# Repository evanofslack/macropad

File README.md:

# MacroPad

Macropad utilizing the Raspberry Pi Pico. 3 layers of functionality, 6 switches, and 1 rotary encoder switch. Implements CircuitPython HID libraries and Adafruit matrix keypad library. Custom PCB designed in KiCAD (Gerbers can be found in the folder). Custom case designed in SolidWorks featuring a lasercut acrylic plates and a 3D printed base.

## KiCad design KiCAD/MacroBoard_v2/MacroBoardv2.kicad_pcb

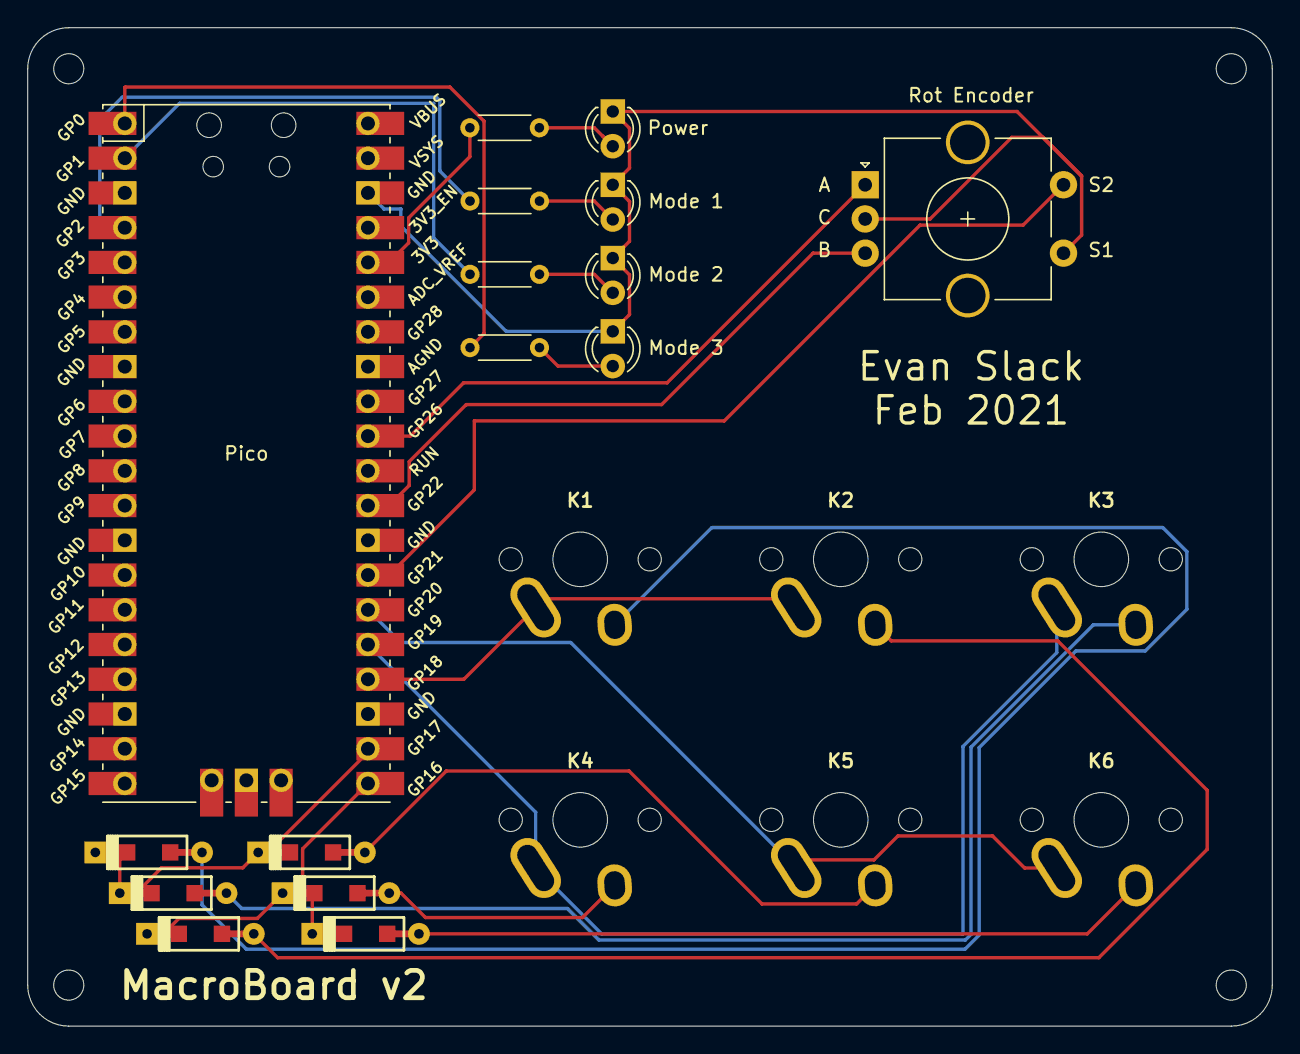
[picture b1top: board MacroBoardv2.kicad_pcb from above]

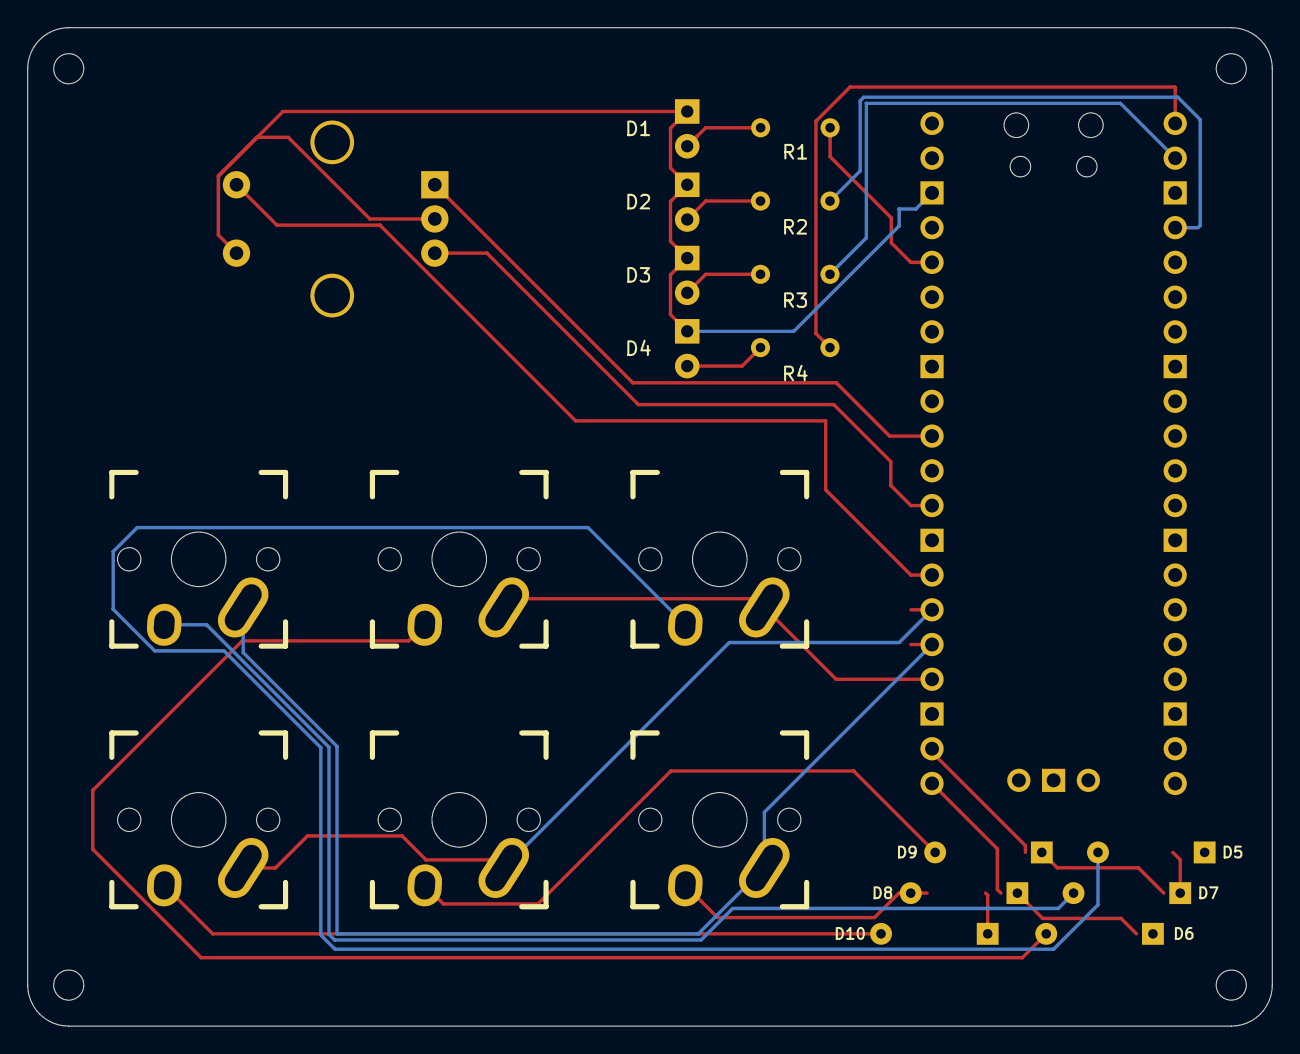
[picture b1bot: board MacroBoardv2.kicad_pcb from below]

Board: 2 copper layers, 91.0 x 73.0 mm, 22 parts (6 on the bottom side), 23 nets.

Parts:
D1, D2, D3, D4: LED; LED_D3.0mm
D5, D6, D7, D8, D9, D10: D; D_SOD123_axial
K1, K2, K3, K4, K5, K6: KEYSW; Mx_Alps_100
Pico: PICO_RP2040; RPi_Pico_SMD_TH
R1, R2, R3, R4: R; R_Axial_DIN0204_L3.6mm_D1.6mm_P5.08mm_Horizontal
Rot Encoder: Rotary_Encoder_Switch; RotaryEncoder_Alps_EC11E-Switch_Vertical_H20mm_CircularMoun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

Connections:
+5V: D1.1, D2.1, D3.1, D4.1, Pico.38, Rot Encoder.C, Rot Encoder.S1
/A_PIN: Pico.31, Rot Encoder.A
/B_PIN: Pico.29, Rot Encoder.B
/ROT_SW: Pico.27, Rot Encoder.S2
/col0: K1.1, K2.1, Pico.24
/col1: K3.1, K4.1, Pico.25
/col2: K5.1, K6.1, Pico.26
/row0: D5.1, D7.1, D9.1, Pico.22
unnamed: D1.2, R1.2
unnamed: D2.2, R2.1
unnamed: D3.2, R3.1
unnamed: D4.2, R4.1
unnamed: D5.2, K1.2
unnamed: D6.2, K2.2
unnamed: D7.2, K3.2
unnamed: D8.2, K4.2
unnamed: D9.2, K5.2
unnamed: D6.1, D8.1, D10.1, Pico.21
unnamed: D10.2, K6.2
unnamed: Pico.36, R1.1
unnamed: Pico.4, R2.2
unnamed: Pico.2, R3.2
unnamed: Pico.1, R4.2

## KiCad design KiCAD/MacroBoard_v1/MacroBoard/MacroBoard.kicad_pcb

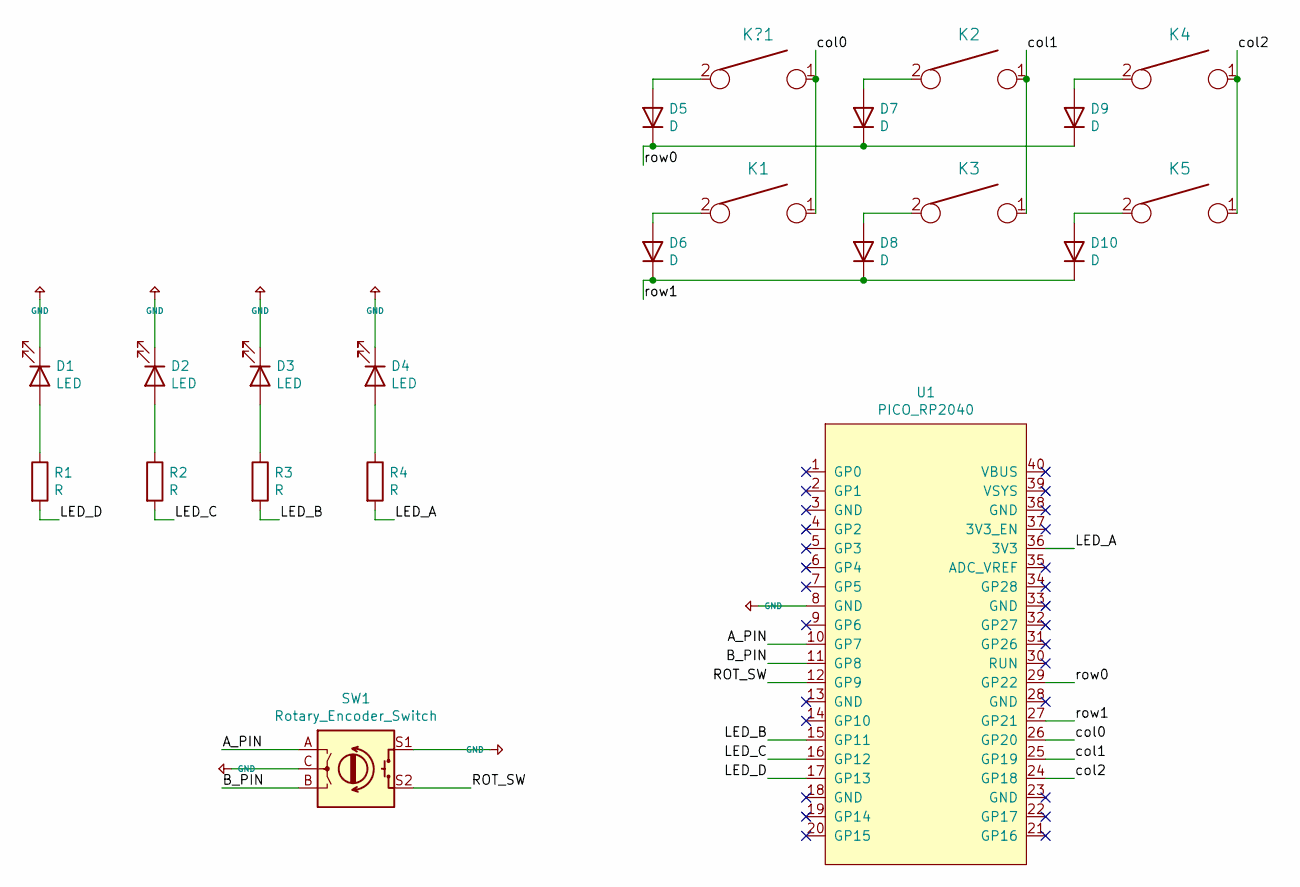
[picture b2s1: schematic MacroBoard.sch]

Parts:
D1, D2, D3, D4: LED; LED_D5.0mm
D5, D6, D7, D8, D9, D10: D; D_SOD123_axial
K1, K2, K3, K4, K5: KEYSW; Mx_Alps_100
K?1: KEYSW; Mx_Alps_100
R1, R2, R3, R4: R; R_Axial_DIN0204_L3.6mm_D1.6mm_P1.90mm_Vertical
SW1: Rotary_Encoder_Switch; RotaryEncoder_Alps_EC11E-Switch_Vertical_H20mm_CircularMoun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
U1: PICO_RP2040; RPi_Pico_SMD_TH

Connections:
+5V: D1.1 (K), D2.1 (K), D3.1 (K), D4.1 (K), SW1.C, SW1.S1, U1.8 (GND)
/A_PIN: SW1.A, U1.10 (GP7)
/B_PIN: SW1.B, U1.11 (GP8)
/LED_A: R4.2, U1.36 (3V3)
/LED_B: R3.2, U1.15 (GP11)
/LED_C: R2.2, U1.16 (GP12)
/LED_D: R1.2, U1.17 (GP13)
/ROT_SW: SW1.S2, U1.12 (GP9)
/col0: K1.1, K?1.1, U1.26 (GP20)
/col1: K2.1, K3.1, U1.25 (GP19)
/col2: K4.1, K5.1, U1.24 (GP18)
/row0: D5.1 (K), D7.1 (K), D9.1 (K), U1.29 (GP22)
/row1: D6.1 (K), D8.1 (K), D10.1 (K), U1.27 (GP21)
unnamed: D1.2 (A), R1.1
unnamed: D2.2 (A), R2.1
unnamed: D3.2 (A), R3.1
unnamed: D4.2 (A), R4.1
unnamed: D5.2 (A), K?1.2
unnamed: D6.2 (A), K1.2
unnamed: D7.2 (A), K2.2
unnamed: D8.2 (A), K3.2
unnamed: D9.2 (A), K4.2
unnamed: D10.2 (A), K5.2

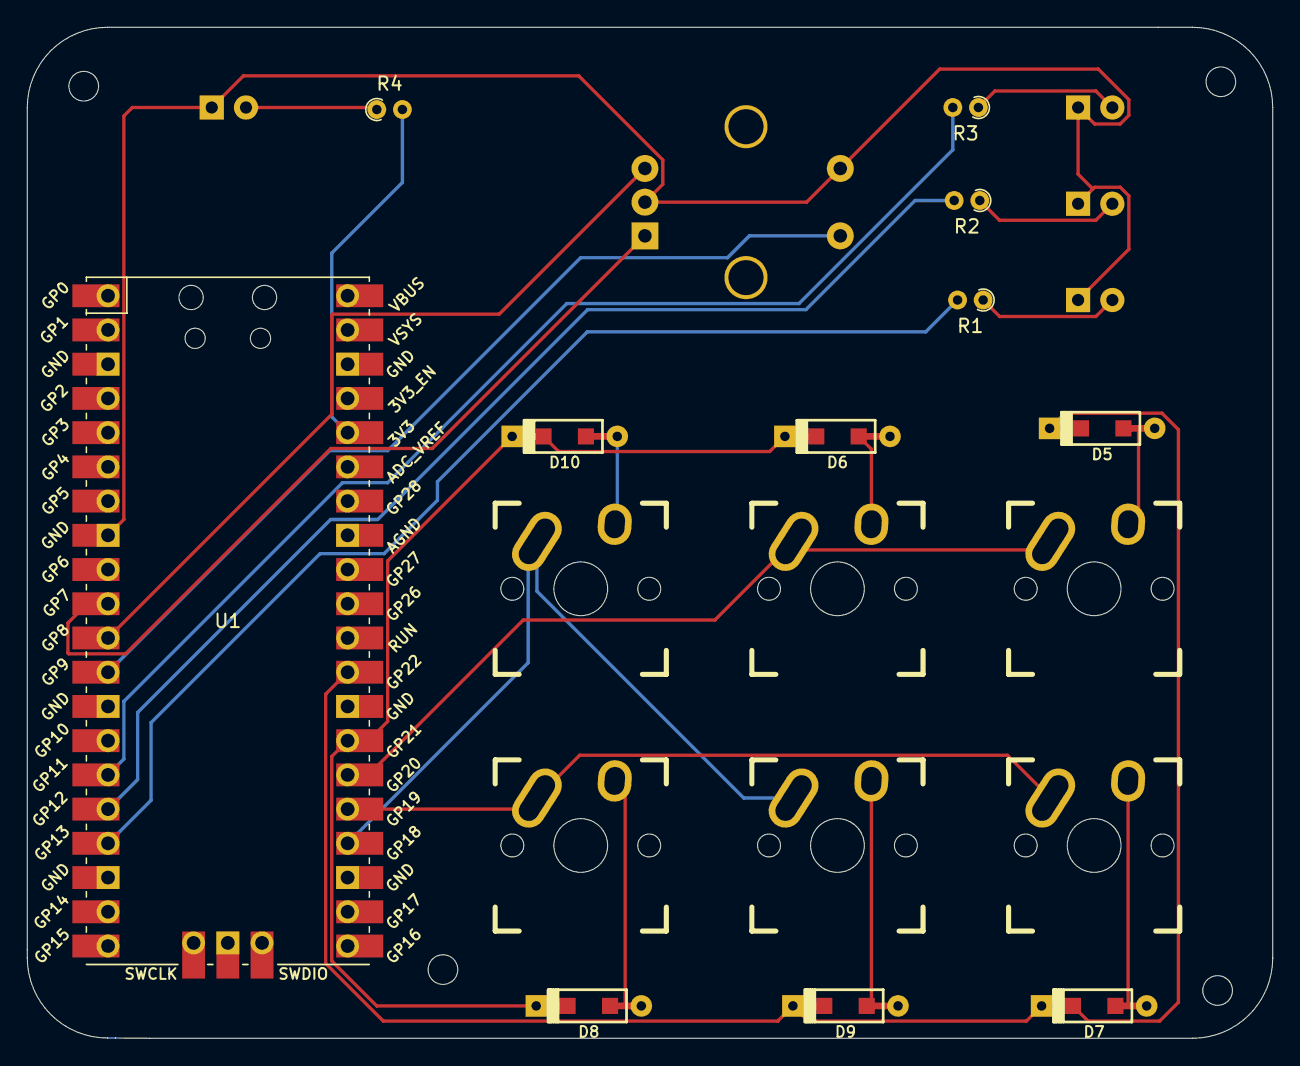
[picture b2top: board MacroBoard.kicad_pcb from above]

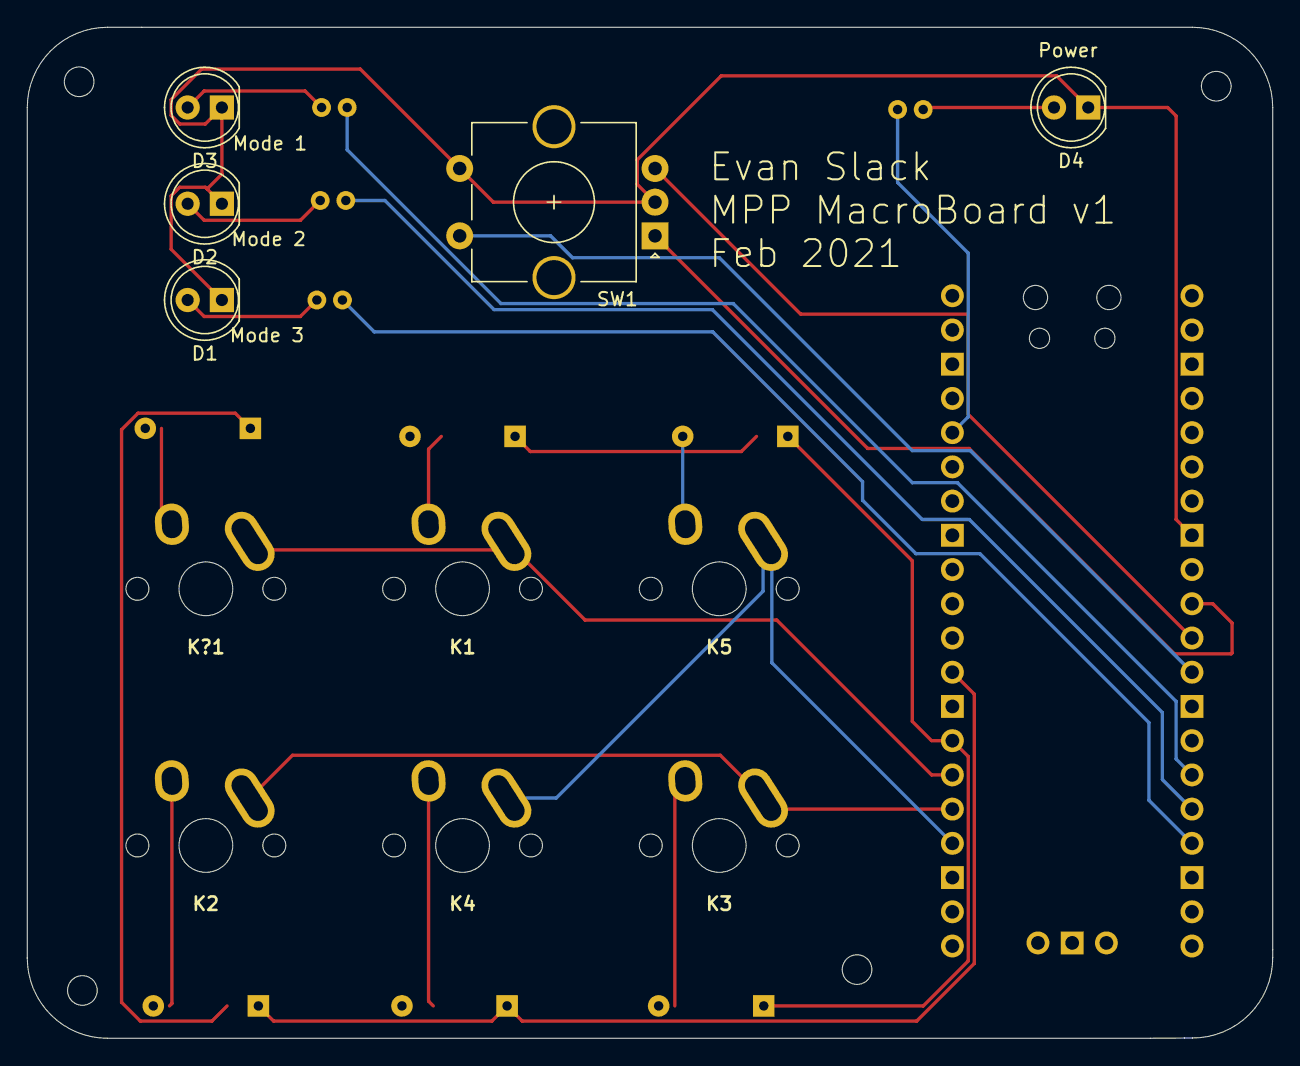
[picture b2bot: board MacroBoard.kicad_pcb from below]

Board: 2 copper layers, 92.4 x 75.0 mm, 26 parts (5 on the bottom side), 23 nets.

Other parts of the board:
 : MountingHole_2.2mm_M2
  : MountingHole_2.2mm_M2
 #2,  #3: MountingHole_2.2mm_M2

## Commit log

2021-02-09 Added pictures
2021-02-09 Added KiCAD files
2021-02-10 Updated Schematic and PCB for revision 2
2021-02-10 Added screenshots of revision 2
2021-02-22 Added SolidWorks Models
2021-02-22 Added latest renders
2021-03-15 Added 360 degree video
2021-03-15 Added exploded view video
2021-03-28 Added initial Circuitpython code
2021-03-28 Updated Assembly
    New stacked acrylic housing and new 3D printed base
2021-03-28 Messed up the commit
2021-03-28 Updated Assembly
    Updated stacked acrylic case and made new 3D printed base
2021-04-15 Added new keyboard layers
2021-04-15 Added Rotary Encoder Example
2021-04-15 Added final build image
2021-04-30 Added Rotating Render Gif
2021-04-30 Added Render Gif
2022-01-05 Remove rtf document
